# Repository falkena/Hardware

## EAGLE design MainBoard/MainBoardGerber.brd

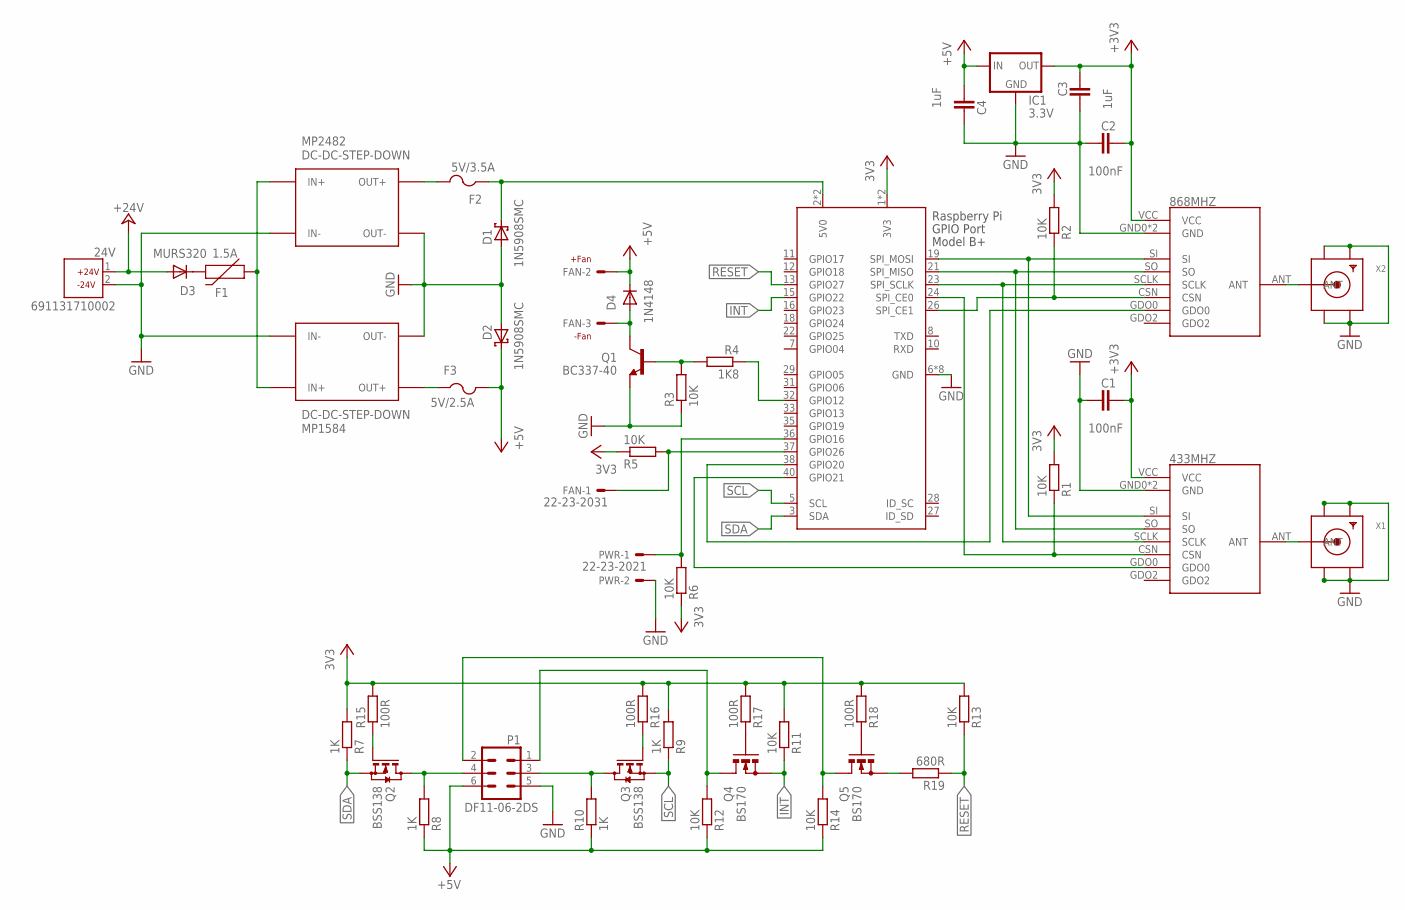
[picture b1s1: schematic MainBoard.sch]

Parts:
24V: 691131710002
433MHZ, 868MHZ: CC1101E07-SMD; E07-M1101S-SMD
C1, C2: 100nF; C0805
C3, C4: 1uF; C0805
D1, D2: 1N5908SMC; SMC
D3: MURS320; SMC
D4: 1N4148; DO35-2V
F1: 1.5A; PTH_11MM
F2: 5V/3.5A; 1812
F3: 5V/2.5A; 1812
FAN: 22-23-2031
IC1: 3.3V; TO92
MP1584: DC-DC-STEP-DOWN; MP1584V
MP2482: DC-DC-STEP-DOWN; MP2482V
P1: DF11-06-2DS; DF11-06DP-2DS
PWR: 22-23-2021
Q1: BC337-40; TO92
Q2, Q3: BSS138; SOT23
Q4, Q5: BS170; SOT54E
R1, R2, R3, R5, R6, R11, R12, R13, R14: 10K; 0204V
R4: 1K8; 0204V
R7, R9: 1K; 0204/5
R8, R10: 1K; 0204V
R15, R16: 100R; 0204/5
R17, R18: 100R; 0204V
R19: 680R; 0204V
RPI: RASPI_BOARD_B+#_4F; RASPI_4_BOARD_B+_FULL
X1, X2: SMACONNECTOR; SMA90_DIP

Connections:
3V3: R1.2, R2.2, R5.1, R6.1, R7.2, R9.2, R11.2, R13.2, R15.2, R16.2, R17.2, R18.2, RPI.1 (3V3), RPI.17 (3V3)
5V0: D1.C, F2.1, RPI.2 (5V0), RPI.4 (5V0)
+3V3: 433MHZ.VCC, 868MHZ.VCC, C1.1, C2.1, C3.1, IC1.3 (OUT)
+5V: C4.2, D2.C, D4.C, F3.2, FAN.2, IC1.2 (IN), P1.6, R8.1, R10.1, R12.1, R14.1
+24V: 24V.1, D3.A
GND: 24V.2, 433MHZ.GND0 (GND), 433MHZ.GND1 (GND), 868MHZ.GND0 (GND), 868MHZ.GND1 (GND), C1.2, C2.2, C3.2, C4.1, D1.A, D2.A, IC1.1 (GND), MP1584.IN-0 (IN-), MP1584.IN-1 (IN-), MP1584.OUT-0 (OUT-), MP1584.OUT-1 (OUT-), MP2482.IN-, MP2482.OUT-, P1.5, PWR.2, Q1.1 (E), R3.1, RPI.6 (GND), RPI.9 (GND), RPI.14 (GND), RPI.20 (GND), RPI.25 (GND), RPI.30 (GND), RPI.34 (GND), RPI.39 (GND), X1.GND1, X1.GND2, X1.GND3, X1.GND4, X2.GND1, X2.GND2, X2.GND3, X2.GND4
INT: Q4.S, R11.1, RPI.15 (GPIO22)
unnamed: P1.3, Q3.3 (D), R10.2
unnamed: 433MHZ.CSN, R1.1, RPI.24 (SPI_CE0)
unnamed: F2.2, MP2482.OUT+
unnamed: Q5.S, R19.2
unnamed: F3.1, MP1584.OUT+0 (OUT+), MP1584.OUT+1 (OUT+)
unnamed: F1.P$1 (1), MP1584.IN+0 (IN+), MP1584.IN+1 (IN+), MP2482.IN+
unnamed: 433MHZ.ANT, X1.ANTENNA (ANT)
unnamed: D3.C, F1.P$2 (2)
unnamed: 433MHZ.GDO0, RPI.40 (GPIO21)
unnamed: Q1.2 (B), R3.2, R4.2
unnamed: P1.4, Q2.3 (D), R8.2
unnamed: R4.1, RPI.32 (GPIO12)
unnamed: D4.A, FAN.3, Q1.3 (C)
unnamed: 868MHZ.CSN, R2.1, RPI.26 (SPI_CE1)
unnamed: 433MHZ.SCLK, 868MHZ.SCLK, RPI.23 (SPI_SCLK)
unnamed: 433MHZ.SO, 868MHZ.SO, RPI.21 (SPI_MISO)
unnamed: 433MHZ.SI, 868MHZ.SI, RPI.19 (SPI_MOSI)
unnamed: 868MHZ.GDO0, RPI.38 (GPIO20)
unnamed: 868MHZ.ANT, X2.ANTENNA (ANT)
unnamed: PWR.1, R6.2, RPI.36 (GPIO16)
unnamed: FAN.1, R5.2, RPI.37 (GPIO26)
unnamed: Q2.1 (G), R15.1
unnamed: Q3.1 (G), R16.1
unnamed: P1.1, Q4.D, R12.2
unnamed: P1.2, Q5.D, R14.2
unnamed: Q5.G, R18.1
unnamed: Q4.G, R17.1
RESET: R13.1, R19.1, RPI.13 (GPIO27)
SCL: Q3.2 (S), R9.1, RPI.5 (SCL)
SDA: Q2.2 (S), R7.1, RPI.3 (SDA)

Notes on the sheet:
+24V
-24V
-Fan
+Fan

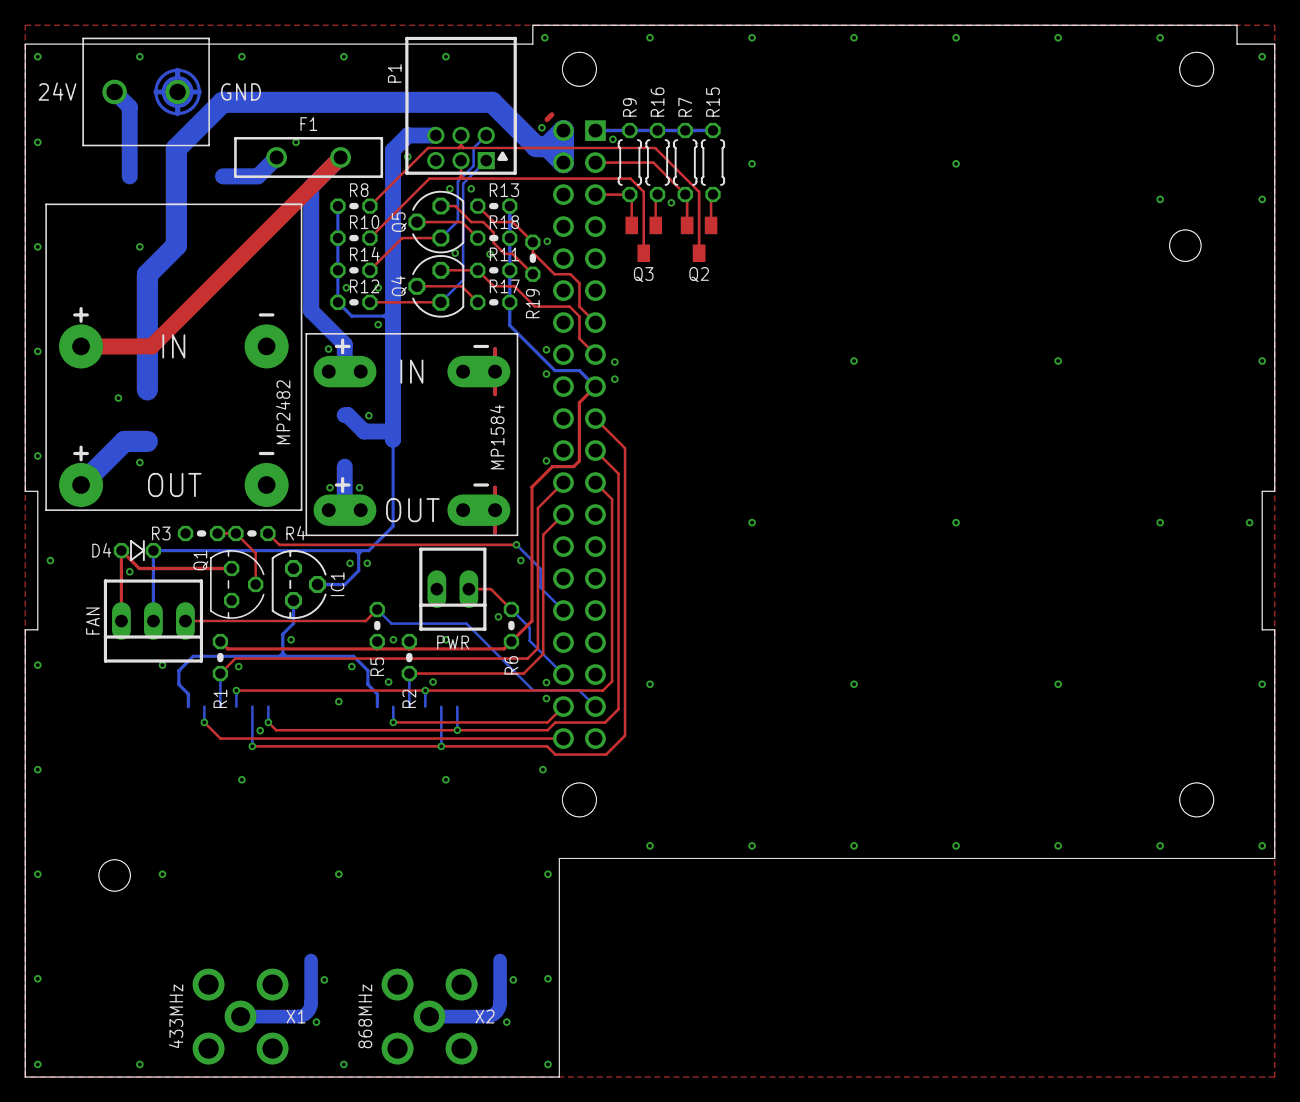
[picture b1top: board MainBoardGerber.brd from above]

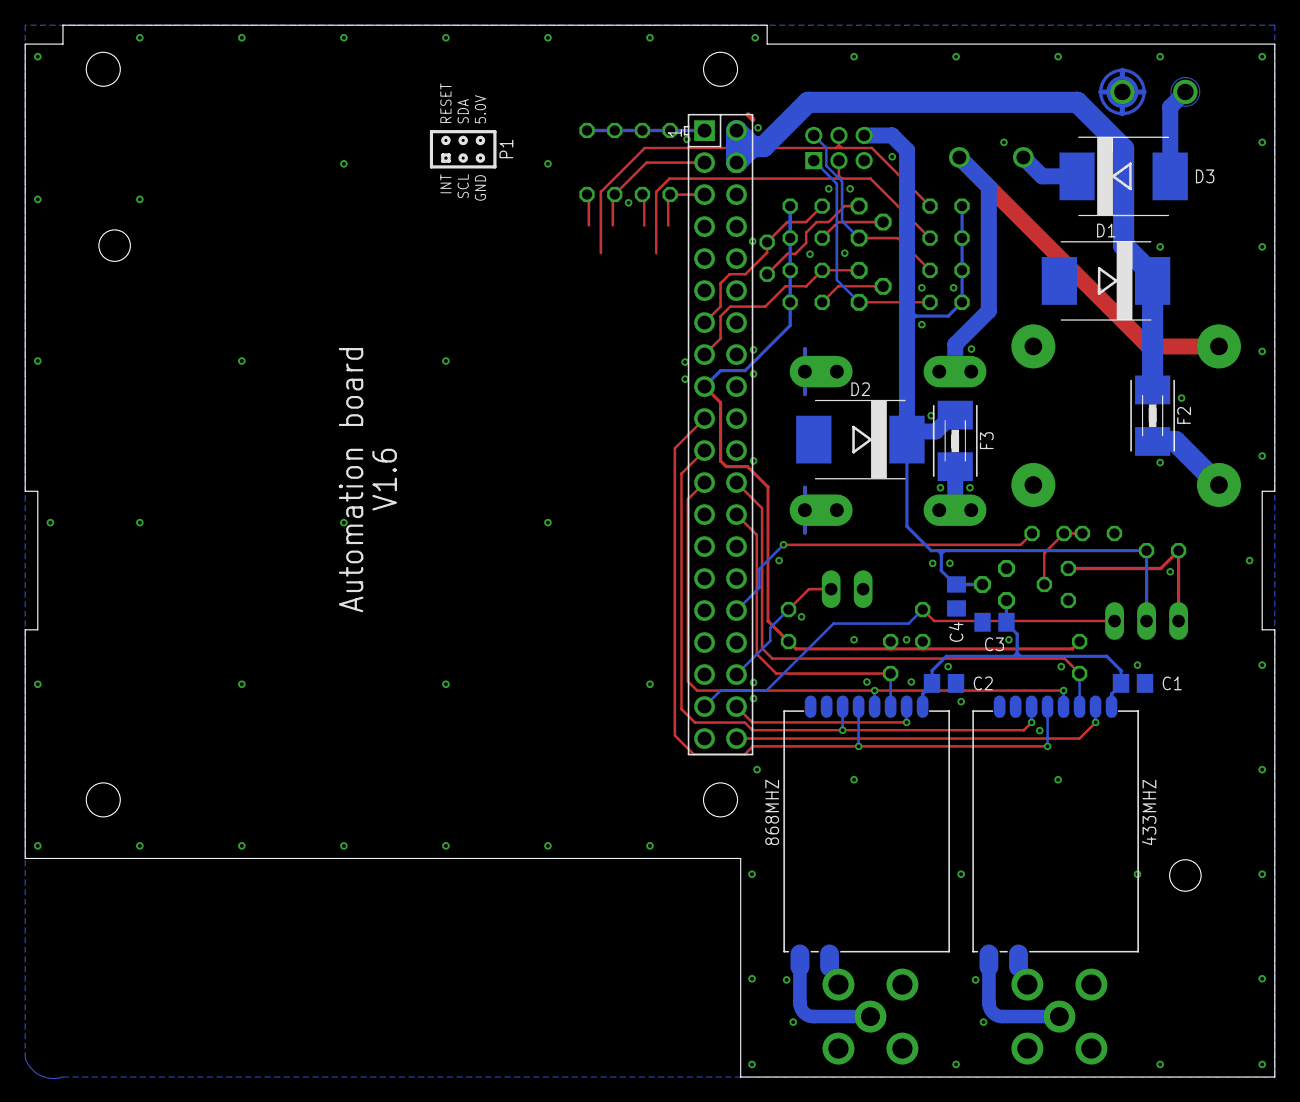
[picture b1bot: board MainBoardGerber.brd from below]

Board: 2 copper layers, 99.2 x 83.5 mm, 47 parts (12 on the bottom side), 37 nets.

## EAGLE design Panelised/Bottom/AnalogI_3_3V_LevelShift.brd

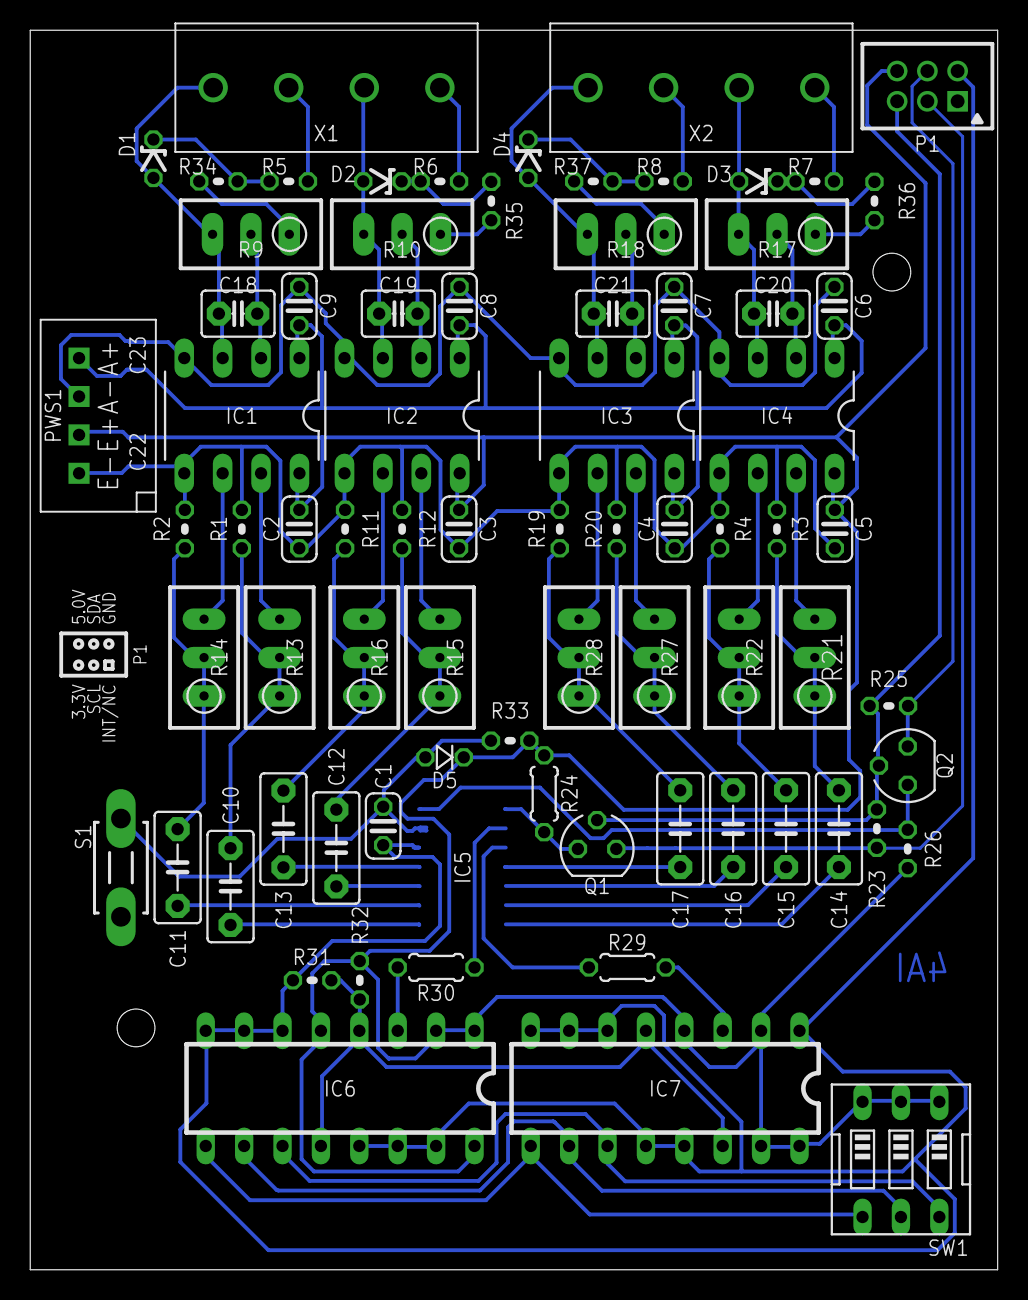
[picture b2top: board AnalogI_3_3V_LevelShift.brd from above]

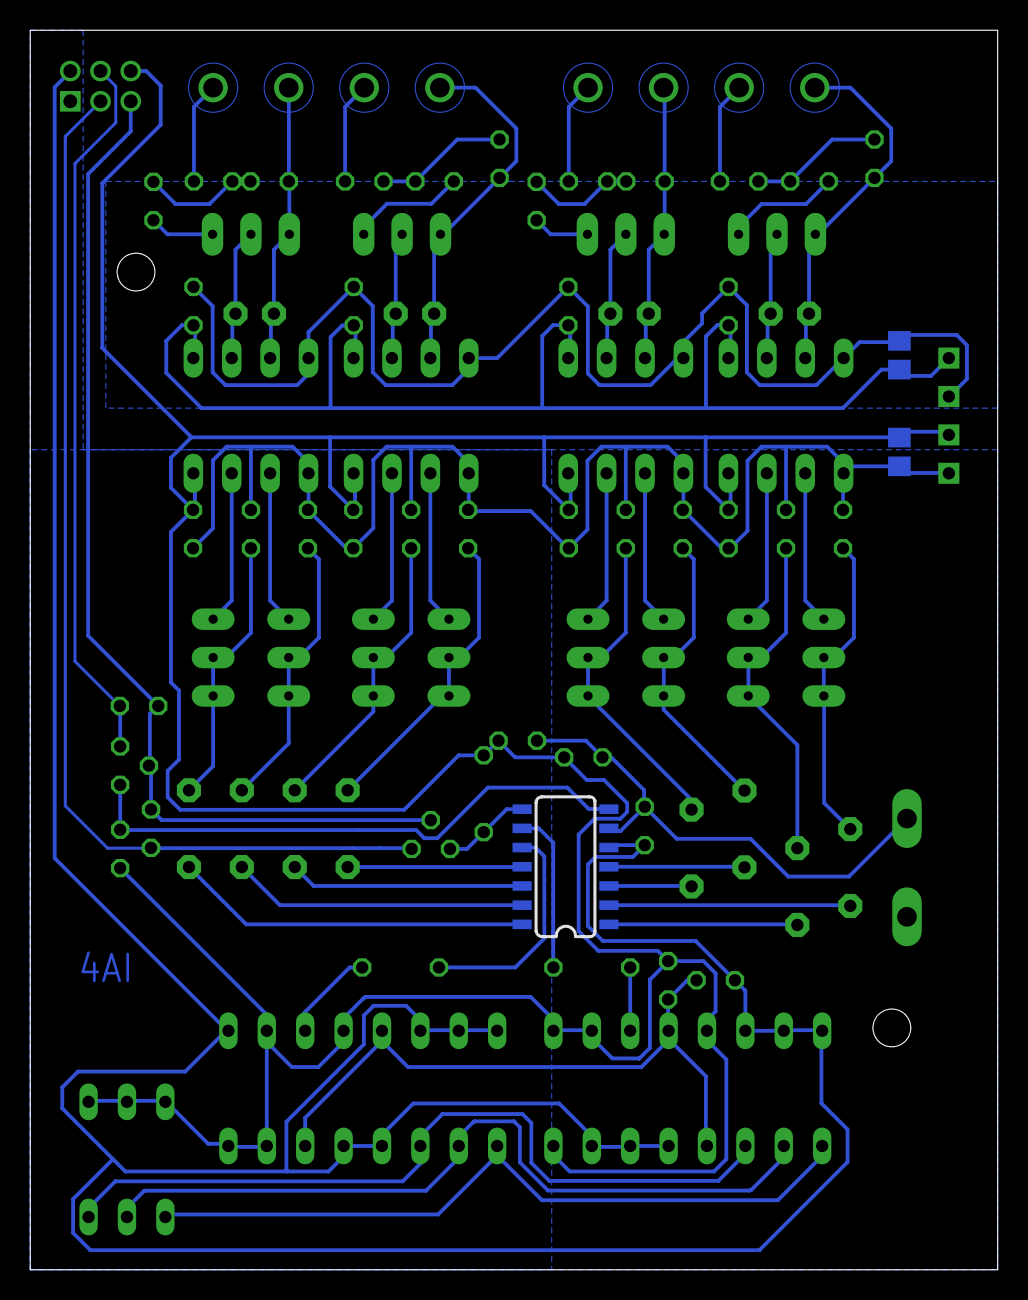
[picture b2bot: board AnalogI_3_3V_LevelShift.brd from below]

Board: 2 copper layers, 64.0 x 82.0 mm, 80 parts (3 on the bottom side), 62 nets.

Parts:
C1, C2, C3, C4, C5, C6, C7, C8, C9: 100nF; C025-024X044
C10, C11, C12, C13, C14, C15, C16, C17: 100nF; C5B3
C18, C19, C20, C21: 10nF; C2.5-3
C22: 4.7uF; C0805
C23: 10uF; C0805
D1, D2, D3, D4: 10V; ZDIO-2.5
D5: 1N4148DO35-2V; DO35-2V
IC1, IC2, IC3, IC4: HCPL-7800; DIL08
IC5: MCP3424SOIC; 14LDSOIC
IC6, IC7: 74HC4051_MUXN; DIL16
P1: DF11-06-2DSA; DF11-06DP-2DSA
PWS1: TME_0505S; TMEXXXXS
Q1, Q2: BS170; SOT54E
R1, R2, R3, R4, R11, R12, R19, R20, R23, R25, R26, R33: 1K; 0204V
R5, R6, R7, R8: 1K2; 0204V
R9, R10, R13, R14, R15, R16, R17, R18, R21, R22, R27, R28: 1K; RTRIM3296W
R24, R29, R30: 1K; 0204/5
R31, R32: 4K7; 0204V
R34, R35, R36, R37: 10K; 0204V
S1: DTS-3
SW1: EDG-03
X1, X2: 691131710004

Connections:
+3V3: P1.5, Q1.G, Q2.G, R23.2, R25.2
+5V: C2.2, C3.2, C4.2, C5.2, C22.1, D5.C, IC1.8, IC2.8, IC3.8, IC4.8, IC6.1, IC6.2, IC6.5, IC6.16, IC7.2, IC7.4, IC7.15, IC7.16, P1.6, PWS1.2, R24.1, R26.2, R32.1, R33.2, SW1.1, SW1.2, SW1.3
GND: C1.2, C2.1, C3.1, C4.1, C5.1, C22.2, IC1.5, IC2.5, IC3.5, IC4.5, IC5.5, IC6.6, IC6.7, IC6.8, IC6.13, IC6.14, IC6.15, IC7.1, IC7.6, IC7.7, IC7.8, IC7.12, IC7.13, P1.2, PWS1.1, R1.1, R2.1, R3.1, R4.1, R11.1, R12.1, R19.1, R20.1, R31.2, S1.2
unnamed: C14.2, IC5.14
unnamed: C15.2, IC5.13
unnamed: C16.2, IC5.12
unnamed: C17.2, IC5.11
unnamed: C19.1, D2.A, IC2.3, R10.3, X1.3
unnamed: R5.1, X1.2
unnamed: D1.C, R5.2, R34.1
unnamed: C6.1, C7.1, C8.1, C9.1, C23.2, IC1.1, IC2.1, IC3.1, IC4.1, PWS1.4
unnamed: IC5.10, R29.1
unnamed: IC5.9, R30.1
unnamed: C18.2, IC1.2, R9.2
unnamed: C19.2, IC2.2, R10.2
unnamed: C10.1, IC5.1
unnamed: C20.2, IC4.2, R17.2
unnamed: C11.1, IC5.2
unnamed: C21.1, D4.A, IC3.3, R18.3, X2.1
unnamed: C12.1, IC5.3
unnamed: C12.2, R12.2, R15.1, R15.2
unnamed: C21.2, IC3.2, R18.2
unnamed: R6.1, X1.4
unnamed: D2.C, R6.2, R35.1
unnamed: IC1.7, R13.3
unnamed: IC1.6, R14.3
unnamed: C10.2, R1.2, R13.1, R13.2
unnamed: IC2.6, R16.3
unnamed: IC2.7, R15.3
unnamed: C11.2, R2.2, R14.1, R14.2
unnamed: R7.1, X2.4
unnamed: C13.2, R11.2, R16.1, R16.2
unnamed: C18.1, D1.A, IC1.3, R9.3, X1.1
unnamed: C13.1, IC5.4
unnamed: D3.C, R7.2, R36.1
unnamed: C6.2, C7.2, C8.2, C9.2, C23.1, IC1.4, IC2.4, IC3.4, IC4.4, PWS1.3
unnamed: R8.1, X2.2
unnamed: D4.C, R8.2, R37.1
unnamed: IC7.3, R29.2
unnamed: IC6.9, IC7.9, SW1.4
unnamed: IC4.7, R21.3
unnamed: IC4.6, R22.3
unnamed: C15.1, R4.2, R22.1, R22.2
unnamed: C20.1, D3.A, IC4.3, R17.3, X2.3
unnamed: C14.1, R3.2, R21.1, R21.2
unnamed: IC3.6, R28.3
unnamed: IC3.7, R27.3
unnamed: C17.1, R19.2, R28.1, R28.2
unnamed: C16.1, R20.2, R27.1, R27.2
unnamed: IC6.10, IC7.10, SW1.5
unnamed: IC6.11, IC7.11, SW1.6
unnamed: IC6.3, R30.2
unnamed: IC6.4, IC6.12, IC7.5, IC7.14, R31.1, R32.2
unnamed: C1.1, D5.A, IC5.6, R33.1, S1.1
unnamed: R9.1, R34.2
unnamed: R10.1, R35.2
unnamed: R17.1, R36.2
unnamed: R18.1, R37.2
unnamed: IC5.8, Q1.D, R24.2
unnamed: IC5.7, Q2.D, R26.1
unnamed: P1.4, Q2.S, R25.1
unnamed: P1.3, Q1.S, R23.1

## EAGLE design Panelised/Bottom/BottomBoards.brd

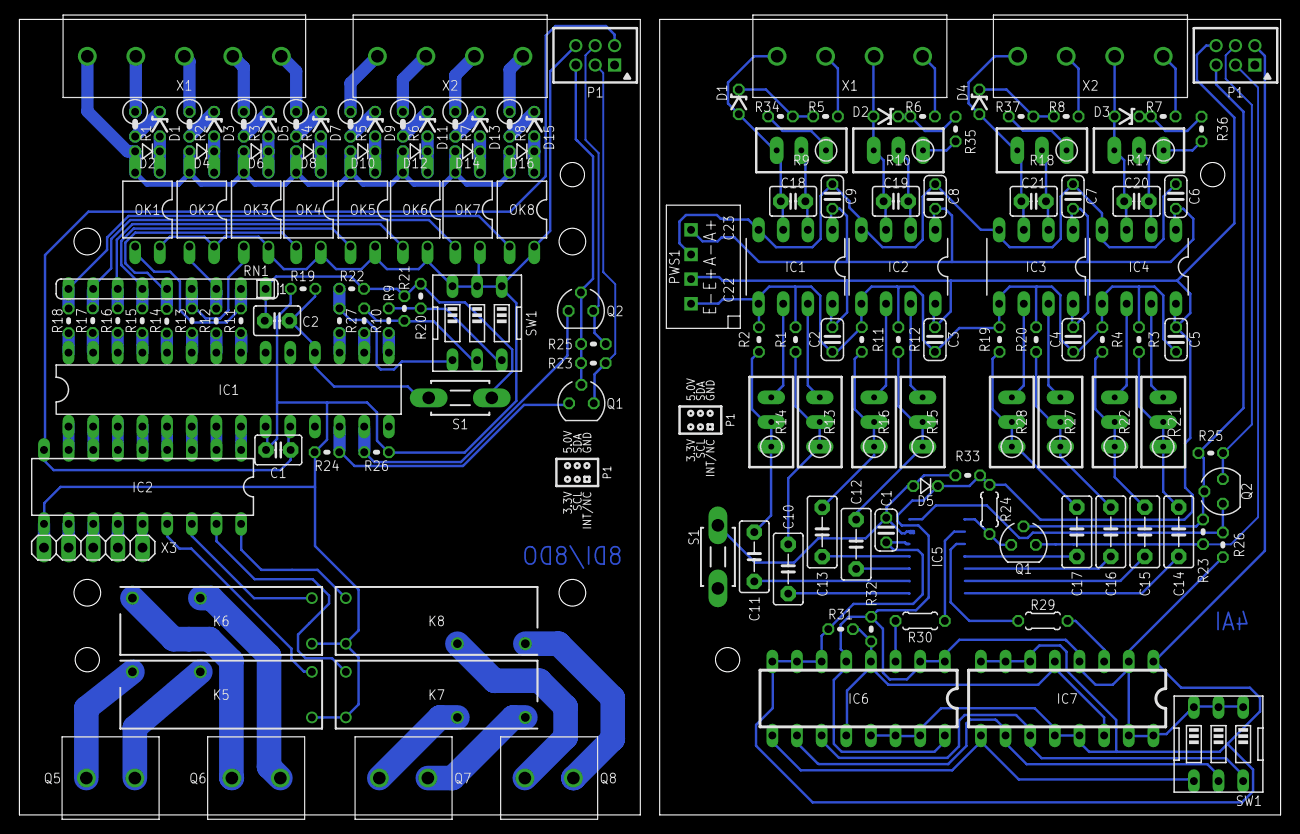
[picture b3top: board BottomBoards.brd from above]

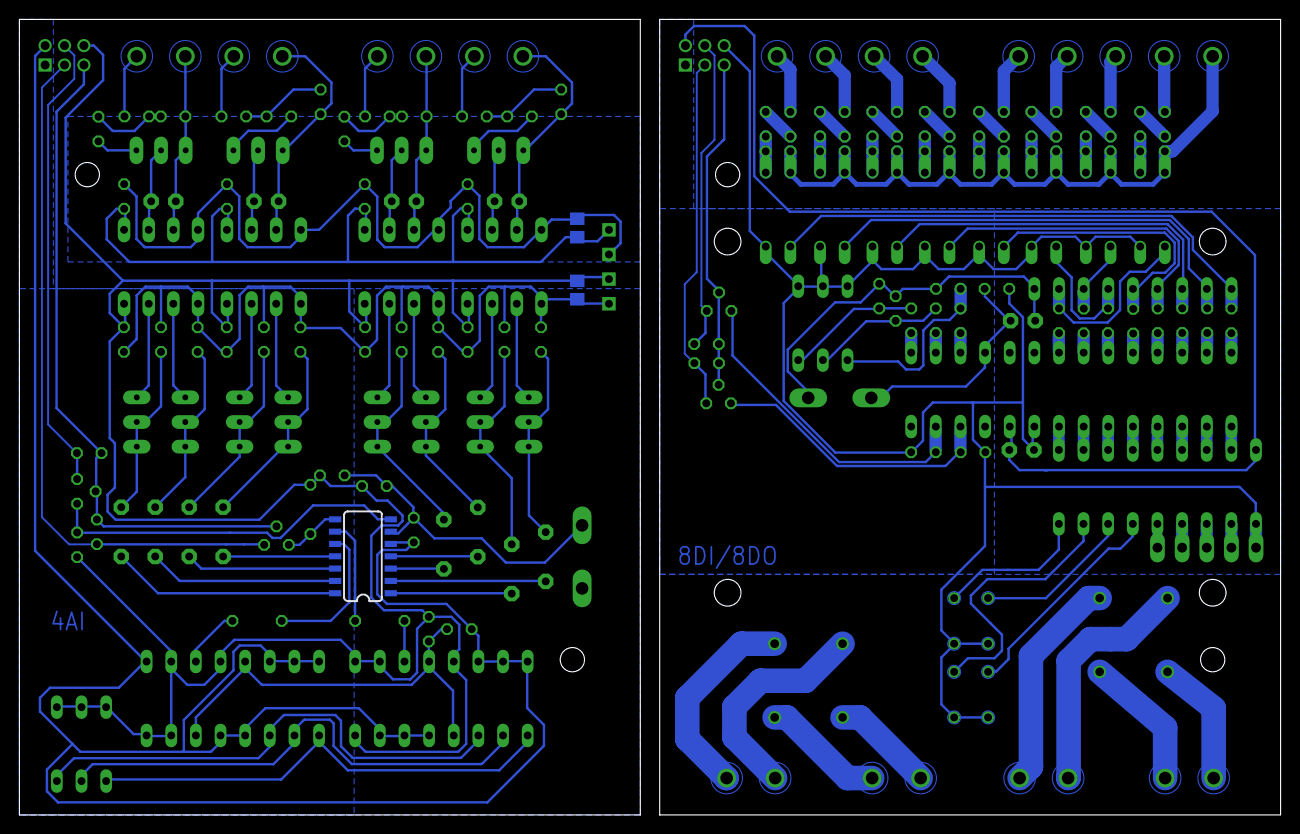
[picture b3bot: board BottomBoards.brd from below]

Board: 2 copper layers, 130.0 x 82.0 mm, 152 parts (3 on the bottom side), 141 nets.

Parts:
C1, C2: 100nF; C2.5-3
C3, C4, C5, C6, C7, C8, C9, C11, C21: 100nF; C025-024X044
C10, C12, C13, C14, C15, C16, C17, C111: 100nF; C5B3
C18, C19, C20, C211: 10nF; C2.5-3
C22: 4.7uF; C0805
C23: 10uF; C0805
D1, D3, D5, D7, D9, D11, D13, D15, D17, D21, D31, D41: 10V; ZDIO-2.5
D2, D4, D6, D8, D10, D12, D14, D16, D51: 1N4148DO35-2V; DO35-2V
IC1: MCP23017SP; DIL28-3
IC2: ULN2803A; DIL18
IC3, IC4, IC11, IC21: HCPL-7800; DIL08
IC5: MCP3424SOIC; 14LDSOIC
IC6, IC7: 74HC4051_MUXN; DIL16
K5, K6, K7, K8: HF46105; HF46
OK1, OK2, OK3, OK4, OK5, OK6, OK7, OK8: PC817; DIL04
P1, P11: DF11-06-2DSA; DF11-06DP-2DSA
PWS1: TME_0505S; TMEXXXXS
Q1, Q2, Q11, Q21: BS170; SOT54E
Q5, Q6, Q7, Q8: 691131710002
R1, R2, R3, R4, R5, R6, R7, R8: 1K2 0.5W; 0207/2V
R9, R10, R11, R12, R13, R14, R15, R16, R17, R18, R23, R24, R25, R26, R27, R28, R31, R33, R41, R110, R111, R121, R191, R201, R231, R251, R261: 1K; 0204V
R19, R20, R21, R22, R34, R35, R36, R37: 10K; 0204V
R29, R30, R241: 1K; 0204/5
R32, R311: 4K7; 0204V
R51, R61, R71, R81: 1K2; 0204V
R91, R101, R131, R141, R151, R161, R171, R181, R211, R221, R271, R281: 1K; RTRIM3296W
RN1: 10K; SIL9
S1, S11: DTS-3
SW1, SW11: EDG-03
X1: 691131710005
X2, X11, X21: 691131710004
X3: 1X05

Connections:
+3V3: P1.5, Q1.G, Q2.G, R23.2, R25.2
+3V31: P11.5, Q11.G, Q21.G, R231.2, R251.2
+5V: C1.2, IC1.9, IC2.10, K5.1, K6.1, K7.2, K8.2, OK1.4, OK2.4, OK3.4, OK4.4, OK5.4, OK6.4, OK7.4, OK8.4, P1.6, R19.2, R24.1, R26.2, SW1.1, SW1.2, SW1.3, X3.1
+5V1: C3.2, C4.2, C5.2, C21.2, C22.1, D51.C, IC3.8, IC4.8, IC6.1, IC6.2, IC6.5, IC6.16, IC7.2, IC7.4, IC7.15, IC7.16, IC11.8, IC21.8, P11.6, PWS1.2, R32.1, R33.2, R241.1, R261.2, SW11.1, SW11.2, SW11.3
GND: C1.1, C2.1, IC1.10, IC2.9, P1.2, R20.1, R21.1, R22.1, RN1.1, S1.1
GND1: C3.1, C4.1, C5.1, C11.2, C21.1, C22.2, IC3.5, IC4.5, IC5.5, IC6.6, IC6.7, IC6.8, IC6.13, IC6.14, IC6.15, IC7.1, IC7.6, IC7.7, IC7.8, IC7.12, IC7.13, IC11.5, IC21.5, P11.2, PWS1.1, R28.1, R31.1, R41.1, R110.1, R111.1, R121.1, R191.1, R201.1, R311.2, S11.2
unnamed: IC1.8, IC2.1
unnamed: IC1.7, IC2.2
unnamed: IC1.6, IC2.3
unnamed: IC1.5, IC2.4
unnamed: IC1.4, IC2.5
unnamed: IC1.3, IC2.6
unnamed: IC1.2, IC2.7
unnamed: IC1.1, IC2.8
unnamed: D3.C, R2.2
unnamed: D1.C, R1.2
unnamed: D2.A, D4.A, D6.A, D8.A, D10.A, D12.A, D14.A, D16.A, OK1.2, OK2.2, OK3.2, OK4.2, OK5.2, OK6.2, OK7.2, OK8.2, X1.1
unnamed: D1.A, D2.C, OK1.1
unnamed: R6.1, X2.2
unnamed: R2.1, X1.3
unnamed: OK1.3, R11.2, RN1.2
unnamed: R3.1, X1.4
unnamed: R7.1, X2.3
unnamed: R1.1, X1.2
unnamed: D3.A, D4.C, OK2.1
unnamed: OK2.3, R12.2, RN1.3
unnamed: D5.C, R3.2
unnamed: R4.1, X1.5
unnamed: D5.A, D6.C, OK3.1
unnamed: R5.1, X2.1
unnamed: OK3.3, R13.2, RN1.4
unnamed: R8.1, X2.4
unnamed: D7.C, R4.2
unnamed: IC2.14, X3.5
unnamed: D7.A, D8.C, OK4.1
unnamed: IC2.13, X3.4
unnamed: OK4.3, R14.2, RN1.5
unnamed: IC2.12, X3.3
unnamed: D9.C, R5.2
unnamed: IC2.11, X3.2
unnamed: D9.A, D10.C, OK5.1
unnamed: R22.2, R27.1, SW1.4
unnamed: OK5.3, R15.2, RN1.6
unnamed: K8.NO, Q8.1
unnamed: D11.C, R6.2
unnamed: K8.COM, Q8.2
unnamed: D11.A, D12.C, OK6.1
unnamed: IC2.15, K5.2
unnamed: OK6.3, R16.2, RN1.7
unnamed: K7.NO, Q7.1
unnamed: D13.C, R7.2
unnamed: K7.COM, Q7.2
unnamed: D13.A, D14.C, OK7.1
unnamed: IC2.16, K6.2
unnamed: OK7.3, R17.2, RN1.8
unnamed: IC1.15, R9.2
unnamed: D15.C, R8.2
unnamed: IC1.16, R10.2
unnamed: D15.A, D16.C, OK8.1
unnamed: IC2.17, K7.1
unnamed: OK8.3, R18.2, RN1.9
unnamed: IC2.18, K8.1
unnamed: C2.2, IC1.18, R19.1, S1.2
unnamed: IC1.12, Q1.D, R24.2
unnamed: IC1.21, R11.1
unnamed: IC1.22, R12.1
unnamed: IC1.13, Q2.D, R26.1
unnamed: IC1.23, R13.1
unnamed: IC1.28, R18.1
unnamed: IC1.27, R17.1
unnamed: IC1.26, R16.1
unnamed: K5.NO, Q5.1
unnamed: IC1.25, R15.1
unnamed: IC1.24, R14.1
unnamed: P1.4, Q2.S, R25.1
unnamed: P1.3, Q1.S, R23.1
unnamed: K5.COM, Q5.2
unnamed: R9.1, R20.2, SW1.6
unnamed: R10.1, R21.2, SW1.5
unnamed: IC1.17, R27.2
unnamed: C6.1, C7.1, C8.1, C9.1, C23.2, IC3.1, IC4.1, IC11.1, IC21.1, PWS1.4
unnamed: K6.NO, Q6.1
unnamed: K6.COM, Q6.2
unnamed: IC5.10, R29.1
unnamed: IC5.9, R30.1
unnamed: C14.2, IC5.14
unnamed: C18.2, IC11.2, R91.2
unnamed: C19.2, IC21.2, R101.2
unnamed: C10.1, IC5.1
unnamed: C20.2, IC4.2, R171.2
unnamed: C111.1, IC5.2
unnamed: C211.1, D41.A, IC3.3, R181.3, X21.1
unnamed: C12.1, IC5.3
unnamed: C12.2, R121.2, R151.1, R151.2
unnamed: C211.2, IC3.2, R181.2
unnamed: R61.1, X11.4
unnamed: C15.2, IC5.13
unnamed: D21.C, R35.1, R61.2
unnamed: IC11.7, R131.3
unnamed: IC11.6, R141.3
unnamed: C10.2, R110.2, R131.1, R131.2
unnamed: IC21.6, R161.3
unnamed: IC21.7, R151.3
unnamed: C111.2, R28.2, R141.1, R141.2
unnamed: R71.1, X21.4
unnamed: C13.2, R111.2, R161.1, R161.2
unnamed: C18.1, D17.A, IC11.3, R91.3, X11.1
unnamed: C16.2, IC5.12
unnamed: C13.1, IC5.4
unnamed: D31.C, R36.1, R71.2
unnamed: C6.2, C7.2, C8.2, C9.2, C23.1, IC3.4, IC4.4, IC11.4, IC21.4, PWS1.3
unnamed: R81.1, X21.2
unnamed: D41.C, R37.1, R81.2
unnamed: IC7.3, R29.2
unnamed: IC6.9, IC7.9, SW11.4
unnamed: IC4.7, R211.3
unnamed: IC4.6, R221.3
unnamed: C15.1, R41.2, R221.1, R221.2
unnamed: C17.2, IC5.11
unnamed: C20.1, D31.A, IC4.3, R171.3, X21.3
unnamed: C14.1, R31.2, R211.1, R211.2
unnamed: IC3.6, R281.3
unnamed: IC3.7, R271.3
unnamed: C17.1, R191.2, R281.1, R281.2
unnamed: C16.1, R201.2, R271.1, R271.2
unnamed: IC6.10, IC7.10, SW11.5
unnamed: IC6.11, IC7.11, SW11.6
unnamed: IC6.3, R30.2
unnamed: C19.1, D21.A, IC21.3, R101.3, X11.3
unnamed: IC6.4, IC6.12, IC7.5, IC7.14, R32.2, R311.1
unnamed: C11.1, D51.A, IC5.6, R33.1, S11.1
unnamed: R34.2, R91.1
unnamed: R35.2, R101.1
unnamed: R36.2, R171.1
unnamed: R37.2, R181.1
unnamed: IC5.8, Q11.D, R241.2
unnamed: R51.1, X11.2
unnamed: IC5.7, Q21.D, R261.1
unnamed: P11.4, Q21.S, R251.1
unnamed: D17.C, R34.1, R51.2
unnamed: P11.3, Q11.S, R231.1

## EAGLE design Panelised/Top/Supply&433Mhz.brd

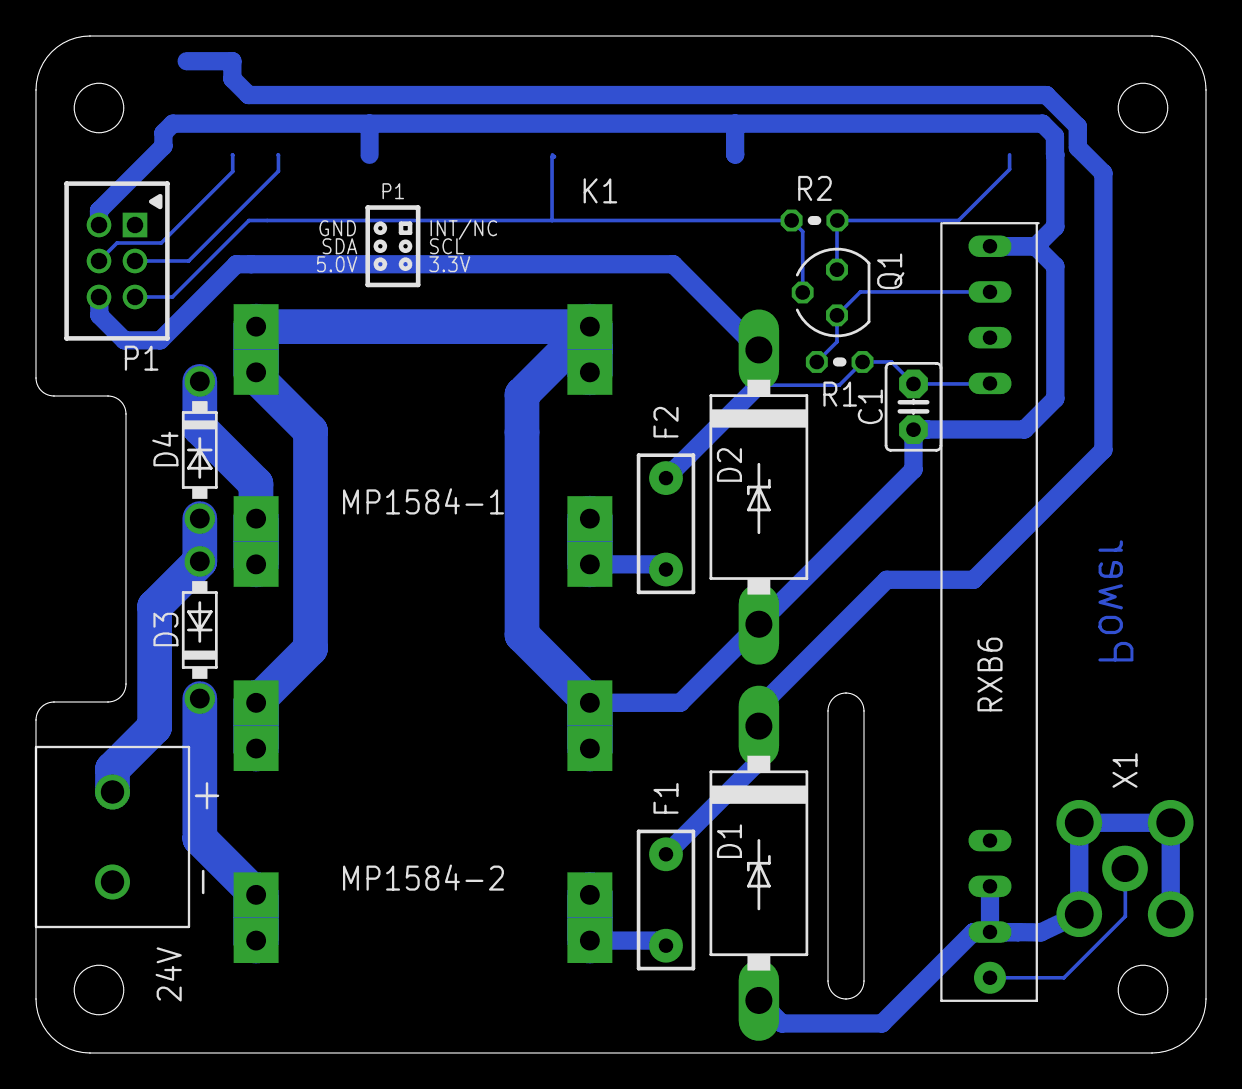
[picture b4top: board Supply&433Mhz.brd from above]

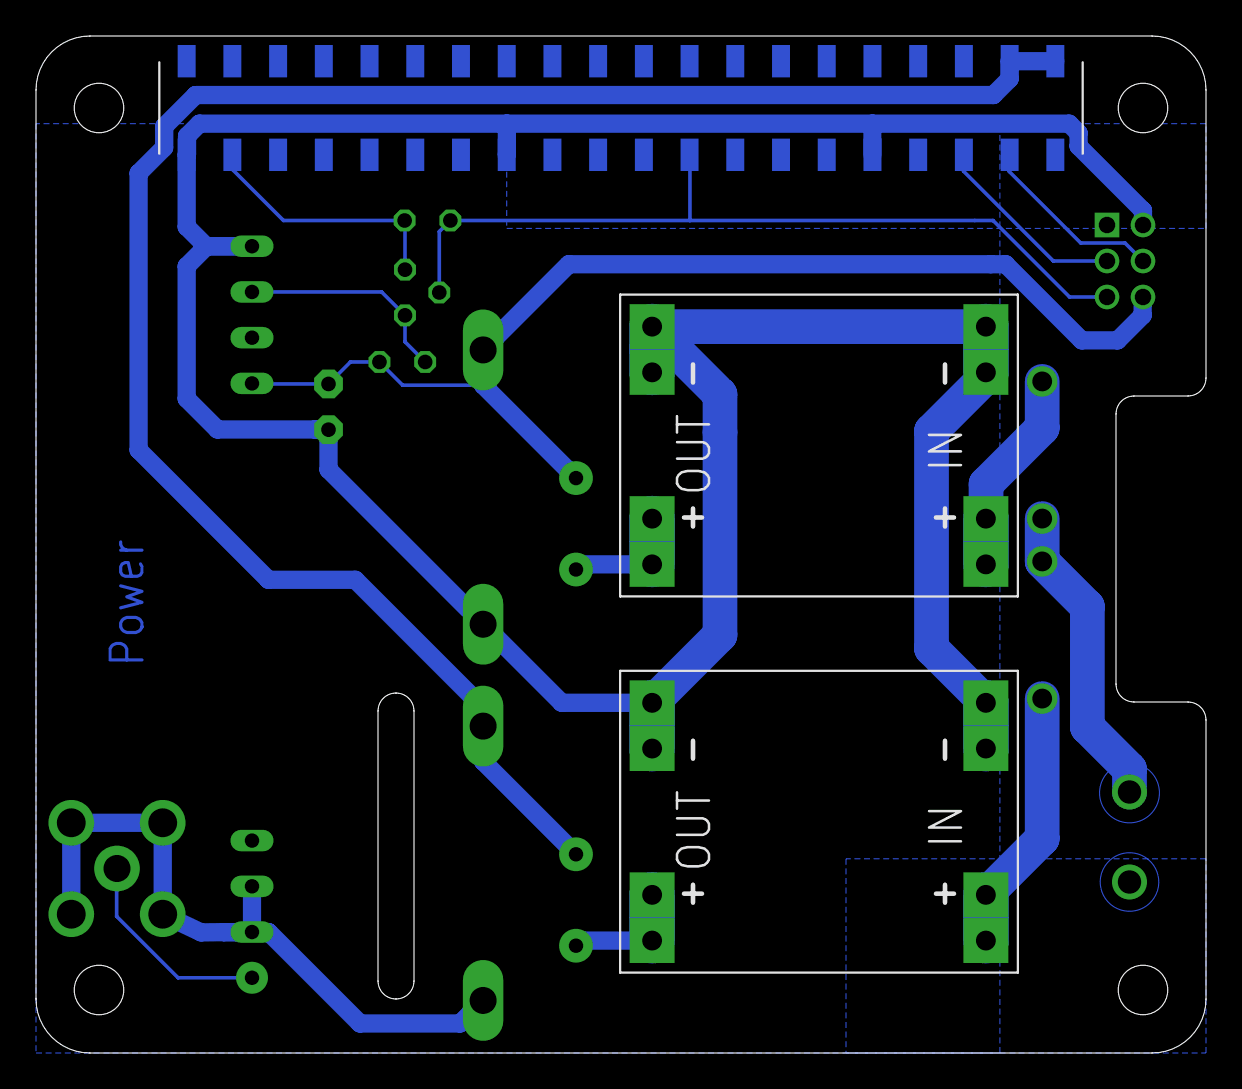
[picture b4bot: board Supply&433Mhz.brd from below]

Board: 2 copper layers, 65.0 x 56.5 mm, 17 parts (3 on the bottom side), 14 nets.

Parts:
24V: 691131710002
C1: 100nF; C2.5-3
D1, D2: 1N5908; C4111-15
D3, D4: SB1H100; DO41-7.6
F1, F2: PTCPTH; PTC
K1: 61004021821
MP1584-1, MP1584-2: DC-DC-STEP-DOWN-MP1584
P1: DF11-06-2DSA; DF11-06DP-2DSA
Q1: BS170; SOT54E
R1, R2: 10K; 0204V
RXB6: WIRELESS-RXB6-5V
X1: SMA90_DIP

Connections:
+24V: 24V.2, D3.A, D4.A
GND: 24V.1, C1.1, D1.A, D2.A, K1.5, K1.13, K1.20, MP1584-1.IN-0, MP1584-1.IN-1, MP1584-1.OUT-0, MP1584-1.OUT-1, MP1584-2.IN-0, MP1584-2.IN-1, MP1584-2.OUT-0, MP1584-2.OUT-1, P1.2, RXB6.GND@1, RXB6.GND@2, RXB6.GND@3, X1.GND1, X1.GND2, X1.GND3, X1.GND4
unnamed: K1.3, P1.3
unnamed: C1.2, D2.C, F2.P$2, P1.6, R1.1, RXB6.VDD@1, RXB6.VDD@2
unnamed: Q1.D, R1.2, RXB6.DATA
unnamed: F1.P$2, MP1584-2.OUT+0, MP1584-2.OUT+1
unnamed: D1.C, F1.P$1, K1.39, K1.40
unnamed: F2.P$1, MP1584-1.OUT+0, MP1584-1.OUT+1
unnamed: D3.C, MP1584-2.IN+0, MP1584-2.IN+1
unnamed: RXB6.ANT, X1.ANTENNA
unnamed: D4.C, MP1584-1.IN+0, MP1584-1.IN+1
unnamed: K1.9, P1.5, Q1.G, R2.2
unnamed: K1.2, P1.4
unnamed: K1.19, Q1.S, R2.1

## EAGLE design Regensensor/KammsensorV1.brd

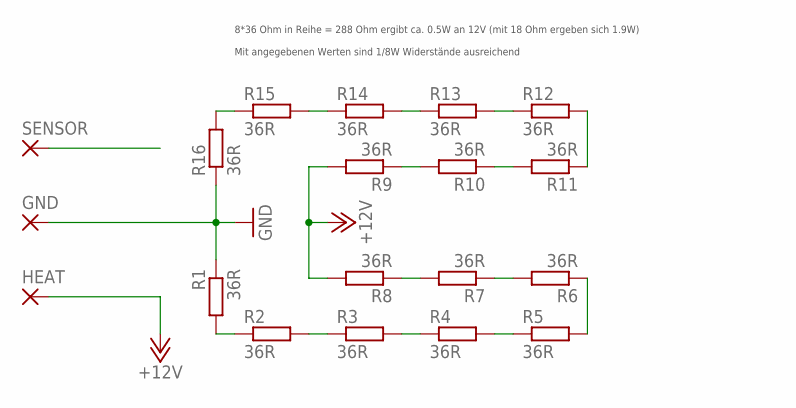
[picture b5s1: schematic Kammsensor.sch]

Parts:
GND: WIREPADSMD5-1,8; 5-1,8
HEAT: WIREPADSMD5-1,8; 5-1,8
R1, R2, R3, R4, R5, R6, R7, R8, R9, R10, R11, R12, R13, R14, R15, R16: 36R; M1206
SENSOR: WIREPADSMD5-1,8; 5-1,8

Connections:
+12V: HEAT.1, R8.2, R9.2
GND: GND.1, R1.1, R16.1
unnamed: R3.2, R4.1
unnamed: R2.2, R3.1
unnamed: R14.1, R15.2
unnamed: R4.2, R5.1
unnamed: R5.2, R6.1
unnamed: R6.2, R7.1
unnamed: R1.2, R2.1
unnamed: R7.2, R8.1
unnamed: R9.1, R10.2
unnamed: R10.1, R11.2
unnamed: R11.1, R12.2
unnamed: R12.1, R13.2
unnamed: R13.1, R14.2
unnamed: R15.1, R16.2
SENSOR: SENSOR.1

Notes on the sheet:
8*36 Ohm in Reihe = 288 Ohm ergibt ca. 0.5W an 12V (mit 18 Ohm ergeben sich 1.9W) Mit angegebenen Werten sind 1/8W Widerstände ausreichend

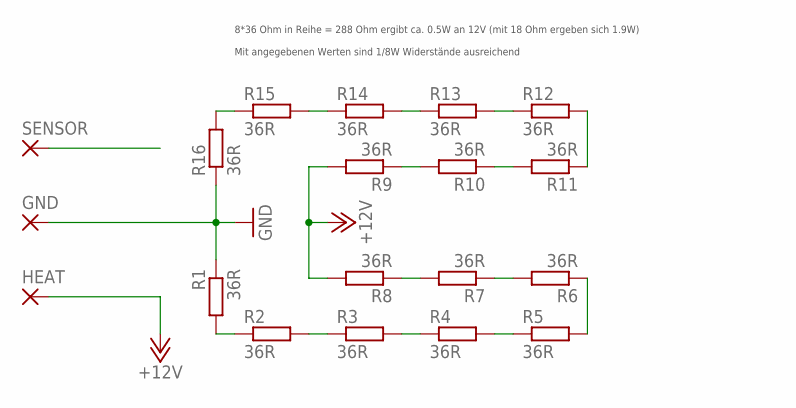
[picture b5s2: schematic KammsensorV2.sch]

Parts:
GND: WIREPADSMD5-1,8; 5-1,8
HEAT: WIREPADSMD5-1,8; 5-1,8
R1, R2, R3, R4, R5, R6, R7, R8, R9, R10, R11, R12, R13, R14, R15, R16: 36R; M1206
SENSOR: WIREPADSMD5-1,8; 5-1,8

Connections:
+12V: HEAT.1, R8.2, R9.2
GND: GND.1, R1.1, R16.1
unnamed: R3.2, R4.1
unnamed: R2.2, R3.1
unnamed: R14.1, R15.2
unnamed: R4.2, R5.1
unnamed: R5.2, R6.1
unnamed: R6.2, R7.1
unnamed: R1.2, R2.1
unnamed: R7.2, R8.1
unnamed: R9.1, R10.2
unnamed: R10.1, R11.2
unnamed: R11.1, R12.2
unnamed: R12.1, R13.2
unnamed: R13.1, R14.2
unnamed: R15.1, R16.2
SENSOR: SENSOR.1

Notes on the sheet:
8*36 Ohm in Reihe = 288 Ohm ergibt ca. 0.5W an 12V (mit 18 Ohm ergeben sich 1.9W) Mit angegebenen Werten sind 1/8W Widerstände ausreichend

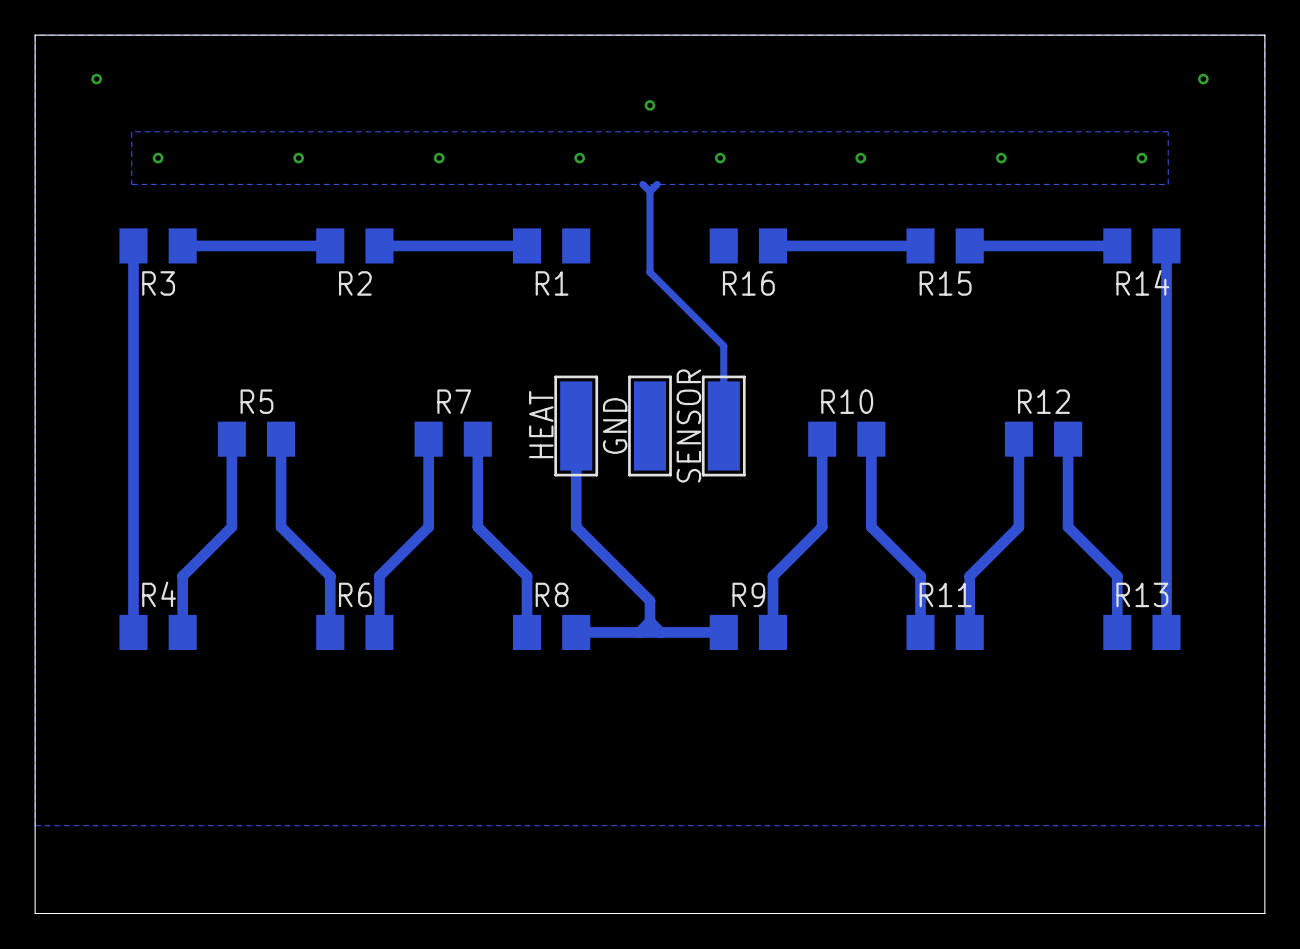
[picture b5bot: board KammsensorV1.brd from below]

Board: 2 copper layers, 70.0 x 50.0 mm, 19 parts (19 on the bottom side), 16 nets.

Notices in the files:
parts and their libraries:
con-wuerth: Copyright: Würth Elektronik
modules: Released under the Open Hardware License: http://www.ohwr.org/licenses/cern-ohl/v1.2
SparkFun-AnalogIC: Licensing:Creative Commons ShareAlike 4.0 International - https://creativecommons.org/licenses/by-sa/4.0
